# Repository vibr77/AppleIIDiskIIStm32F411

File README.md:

# SmartDisk II — Apple II Floppy Emulator

**The Apple II floppy emulator that even copy protection can't tell apart.**

Swap a shelf of aging 5.25″ disks for a single SD card — without giving up an ounce of authenticity. SmartDisk II reproduces the exact timing and behaviour of a real DISK II and UNIDISK 3.5 drive, so your games load and run exactly as they did back in the day — protection schemes and all.

<p align="center">
  <a href="https://www.ebay.fr/itm/306883712221"><b>🛒 Buy a prebuilt board</b></a> ·
  <a href="https://github.com/vibr77/AppleIIDiskIIStm32F411"><b>🔧 Build it yourself</b></a> ·
  <a href="https://discord.gg/ZnzDqC2k"><b>💬 Join the Discord</b></a> ·
  <a href="https://www.r3tr0.net/index.php/smartdisk-ii-documentation/"><b>📖 Documentation</b></a>
</p>

---

## What is it

SmartDisk II is an **open-source hardware floppy-disk emulator for the Apple II**. It plugs into your machine like a real drive, reads disk images straight from an SD card, and lets you browse and mount them from a built-in OLED menu — no PC, no cables, no fuss.

Under the hood it's built on the **STM32F411 ("BlackPill")** and emulates the disk hardware *at the bit level*. That's the difference between *reading a disk image* and *being a disk drive* — and it's why SmartDisk II runs the titles other emulators choke on.

## Why SmartDisk II

- **Bit-perfect accuracy.** Timing is reproduced down to the microsecond, so the Apple II can't tell it apart from a mechanical drive.
- **It beats copy protection.** Fake bits, weak bits, half-tracks, SpiraDisc and more — it passes every scheme tested so far.
- **Your whole collection on one card.** Thousands of disks on a single SD card, browsable on the on-board OLED.
- **Works across the Apple II line.** From the II+ to the IIGS, Disk II and SmartPort — one device covers your fleet.
- **Read *and* write.** Save your progress and modify disks, not just load them.
- **Open source, or ready to run.** Build it from the published files, or order a prebuilt, flashed board and plug in today.

## Browse and boot — right from the Apple II

With **SmartLoader**, you don't even need the SmartDisk II's own buttons for everyday loading. It puts a fast green-screen browser on the Apple II itself: SmartLoader reads the disk images on your SD card and lists them right on screen, so you can scroll through your whole collection and boot any title straight from the Apple II — highlight a disk, press **[B]** to boot, **[R]** to refresh the listing, or **[S]** for settings.

## Copy protection that actually works

Most emulators fall over the moment a disk uses copy protection. SmartDisk II doesn't. By reproducing the original drive's bit-level timing, it satisfies the protection checks that real software relied on — so your original protected images run untouched.

| Copy protection             | Status     |
|:----------------------------|:-----------|
| Fat Track                   | ✅ Passed |
| Weak Bit                    | ✅ Passed |
| Cross-track synchronisation | ✅ Passed |
| Half Track                  | ✅ Passed |
| Data Latch                  | ✅ Passed |
| Timing Bits                 | ✅ Passed |
| E7                          | ✅ Passed |
| Optimal Bit Timing (<4µs)   | ✅ Passed |
| Various Bit Counter         | ✅ Passed |
| SpiraDisc                   | ✅ Passed |

## Compatibility

| Apple II model | Emulation             |
|:---------------|:----------------------|
| II+            | Disk II               |
| II Europlus    | Disk II               |
| IIe            | Disk II               |
| IIc (ROM 4)    | Disk II + SmartPort   |
| IIGS           | Disk II + SmartPort   |

SmartPort emulation is also available on the IIc (ROM 4.x), IIGS, and on the II+/IIe with a Liron or SoftSP6 card.

## Supported disk formats

| Format  | Read | Write |
|:--------|:-----|:------|
| WOZ 2.0 | ✅   | ✅    |
| DSK     | ✅   | ✅    |
| PO      | ✅   | ✅    |
| 2MG     | ✅   | ✅    |
| WOZ 1.0 | ✅   | —     |
| NIC     | ✅   | —     |

## Features at a glance

- **Three drives in one** — DISK II 5.25″, SmartPort HD, and UNIDISK 3.5 emulation
- **On-board navigation** — browse, mount and unmount images from the 0.96″ OLED with four buttons
- **Big images, no sweat** — 32 MB images and full Total Replay collections run smoothly
- **Modern software too** — loads GS/OS on the IIGS; runs titles like Arkanoid from 2MG
- **SmartLoader** built in — browse and boot from the Apple II screen itself
- **Actively developed** — frequent firmware releases with the latest improvements

## See it in action

- ▶ [Total Replay & 32 MB images, running smoothly](https://www.youtube.com/watch?v=Sws6IjnWDGQ)
- ▶ [Arkanoid, loaded from a 2MG image](https://www.youtube.com/watch?v=U3N-gej0NLk)
- ▶ [Loading GS/OS on the IIGS](https://www.youtube.com/watch?v=gZH2njO4CEQ)

## Get your SmartDisk II

**Buy a prebuilt board.** Don't want to solder? Order a ready-to-use, fully flashed and tested SmartDisk II and plug in today → [Order on eBay](https://www.ebay.fr/itm/306883712221)

**Build it yourself.** Everything you need is open source — KiCad PCB, Gerber files, bill of materials, 3D-printable case, firmware releases and full source code. **Current production board: Revision 8**, recommended for self-builds.

**Get help & follow along.** Join the community on [Discord](https://discord.gg/6y2Zdazy), or read the full development story on [AppleFritter](https://www.applefritter.com/content/apple-ii-disk-emulator-using-stm32).

## Tech specs

- **MCU:** STM32F411 ("BlackPill") — chosen for CPU speed, >60 kB SRAM and 4-bit SDIO
- **Storage:** SD card, FAT32 (4-bit SDIO for speed) — a quality, known-brand card is recommended
- **Display:** 0.96″ OLED (SSD1306) with four-button navigation
- **Board:** Production Revision 8, fully tested
- **Licence:** open source for non-commercial use with attribution

---

# Build & developer guide

Everything below is for people building, flashing, or hacking on the SmartDisk II. The full end-user manual (wiring, SD-card prep, menu walkthrough) lives in the [online documentation](https://www.r3tr0.net/index.php/smartdisk-ii-documentation/).

## Firmware

The latest firmware (see the releases on the right-hand side of the GitHub page) requires **bootloader v0.14 or v0.16**. Version 0.15 is **not** compatible and causes issues with the IIGS SmartPort. It is recommended to update the bootloader to the latest version.

There are two release types:

- **BIN** — classic binary, uploaded via ST-Link, starting at `0x08000000`.
- **UF2** — first upload the custom bootloader via ST-Link, then connect USB and double-click the NRST button to drag-and-drop the UF2 release onto the STM32. **Warning:** with the bootloader, flash from `0x08000000` to `0x08100000` becomes read-only (use ST-Link tooling to change the STM32 register to reverse this).

## Project structure

| Directory            | Description                                          |
|:---------------------|:-----------------------------------------------------|
| `./hardware`         | KiCad project                                        |
| `./hardware/gerber`  | Gerber release to produce the PCB                    |
| `./hardware/bom`     | Bill of materials                                    |
| `./core`             | Firmware source code                                 |
| `./bootloader`       | Bootloader                                           |
| `./Middleware`       | Libraries used                                       |
| `./FATFS`            | FATFS wrapper                                         |
| `./doc`              | Documentation used as reference                      |
| `./3DPrintCase`      | 3D-print files & Fusion 360 source for the case      |

## SD card

The SD card must use a **FAT32 file system with 64 sectors of 512 bytes each per cluster (32 KB clusters)**.

To format the card under Linux:

```bash
mkfs.fat -F 32 -s 64 /dev/sdX
```

Windows 10/11 does **not** format the card the right way. A config-menu option is provided directly on the SmartDisk II to format the SD card correctly. Note that some SD cards have very poor read/write rates — use a known brand to avoid wasting your time.

## Important notes

- The ST-Link programmer should **never** be connected at the same time as either USB or the Apple II — its voltage regulator is fragile.
- The **J1 PWR** jumper (top-right of the PCB) enables +5 V from the Apple II to the STM32.
- OLED screen: be careful of the power-pin order; some versions have the pins inverted.
- R1, R2, R3 are not needed.
- Before hardware Rev 3, the board is not compatible with the IIGS & IIc — the trace between IDC pins 5 & 7 needs to be cut.
- Hardware design may evolve; new software releases might not work with older hardware revisions.

## Hardware design principles

The STM32F4x is preferred over the STM32F1 for CPU frequency, available SRAM (>60 kB), and (on the F411) SDIO. Timing is critical on this project, especially to pass copy protection.

A DISK II floppy track is about 50,000 bits, and shifting from one track to another must respect specific timing rules. After many design iterations, the chosen approach loads a **single track in memory** and uses the **4-bit SDIO port** for SD card read/write speed — avoiding adjacent-track management and complex buffer copies.

The Apple II expects data at a precise pace of **1 bit every 4 µs (32 × 125 ns)**. Three options were considered:

1. SDIO with DMA — frees the CPU, but SPI sends 8 bits at a time; WOZ tracks aren't 8-bit aligned, which introduces bit misalignment and corrupted data on protected images.
2. Assembly with CPU-cycle counting & GPIO bit-banging — poor reliability, discarded.
3. **Timer-interrupt-triggered GPIO bit-banging (chosen)** — frees CPU time for OLED updates and button handling, makes fake-bit/protection mechanisms easy to address, and allows fine timing control (e.g. 3.8 µs vs 4 µs that some games use).

The write process mirrors the read process with a dedicated timer overflowing every 4 µs; polarity inversion is handled in software with an XOR rather than external circuitry.

### STM32 pin mapping

**Head-positioning stepper (external interrupts):**
`PA0` STEP0 / ExtI0 · `PA1` STEP1 / ExtI1 · `PA2` STEP2 / ExtI2 · `PA3` STEP3 / ExtI3

**Other GPIO:**
`PB8` SELECT (ExtI8, HIGH on Disk II controller — A2 powered on) · `PB9` WR Request (ExtI9, active LOW when writing) · `PA4` Device Enable (ExtI4, active LOW) · `PB2` WR Protect · `PA7` WR Data · `PB0` RD Data · `PA11` _DISK3.5

**Buttons (ExtI 9-15, TIM4 debounce):**
`PC13` BTN_DOWN · `PC14` BTN_UP · `PC15` BTN_ENTR · `PB12` BTN_RET

**SD card (SDIO, clock ÷2):**
`PB4` D0 · `PA8` D1 · `PA9` D2 · `PB5` D3 · `PA6` CMD · `PB15` CK

**OLED SSD1306 (I²C):** `PB6` SCL · `PB7` SDA

**UART:** `PA15` TX · `PB3` RX

**Timers:**
- **TIM2** — manages WR_DATA; ETR1 slave-reset mode resyncs with the Apple II write pulse (3.958 µs instead of 4 µs) on every rising edge.
- **TIM3** — manages RD_DATA.
- **TIM4** — internal (no PWM), debouncer for the control buttons.

## Software design principles

Built on:

- STM32 HAL drivers from STMicro
- FATFS 0.15 (note: STM32CubeMX overrides to 0.11)
- cJSON for the configuration file (tweaked to work with FATFS)
- SSD1306 library with DMA

Maximum track size is `13 × 512 × 8 = 53,248` bits (6,656 bytes), held in `DMA_BIT_TX_BUFFER[6656]`. `weakBitTank` (uint8 array) and `fakeBitTank` (char array) manage copy-protection mechanisms.

**Key functions:**

- `TIM3_IRQHandler` — bit-bangs the GPIO to send track data every 4 µs (or less, per WOZ config) to the Apple II.
- `TIM2_IRQHandler` — handles data sent from the Apple II for writing; uses a software XOR to detect polarity inversion and writes 1/0 to `DMA_BIT_RX_BUFFER`.
- `irqReadTrack` / `irqWriteTrack` — configure read/write interrupts.
- `getDataBlocksBareMetal(...)` / `setDataBlocksBareMetal(...)` — direct SDIO access to the SD card, faster than FATFS `f_open`. (FATFS is still required to build the file allocation table with correct block addresses.)
- `processDeviceEnableInterrupt` — activates/deactivates the Disk II drive on the DEVICE_ENABLE pin (active LOW).
- `processBtnInterrupt` — handles the four buttons.
- `processDiskHeadMoveInterrupt(...)` — handles the four stepper-motor GPIOs.
- `main()` — orchestrates program execution.

A **ST-Link** programmer is required to upload firmware to the STM32F411.

## Bill of materials

Interactive BOM: [SmartDisk II Bill of Material](https://vibr77.github.io/AppleIIDiskIIStm32F411/hardware/bom/ibom.html)

## Recommended reading

WOZ 2.1 & 1.0 image file references · Tome of Copy Protection · Beneath Apple DOS · Assembly Lines · Understanding the Apple II · PoC‖GTFO issues 10 & 11 · IIGS Firmware Reference · IIc Programmer's Guide to the 3.5 ROM (part 2)

## Licence

This project may be distributed, remixed, adapted and built upon, in any medium or format, **for non-commercial purposes only**, and only with attribution to the creator. Commercial rights are reserved to the author.

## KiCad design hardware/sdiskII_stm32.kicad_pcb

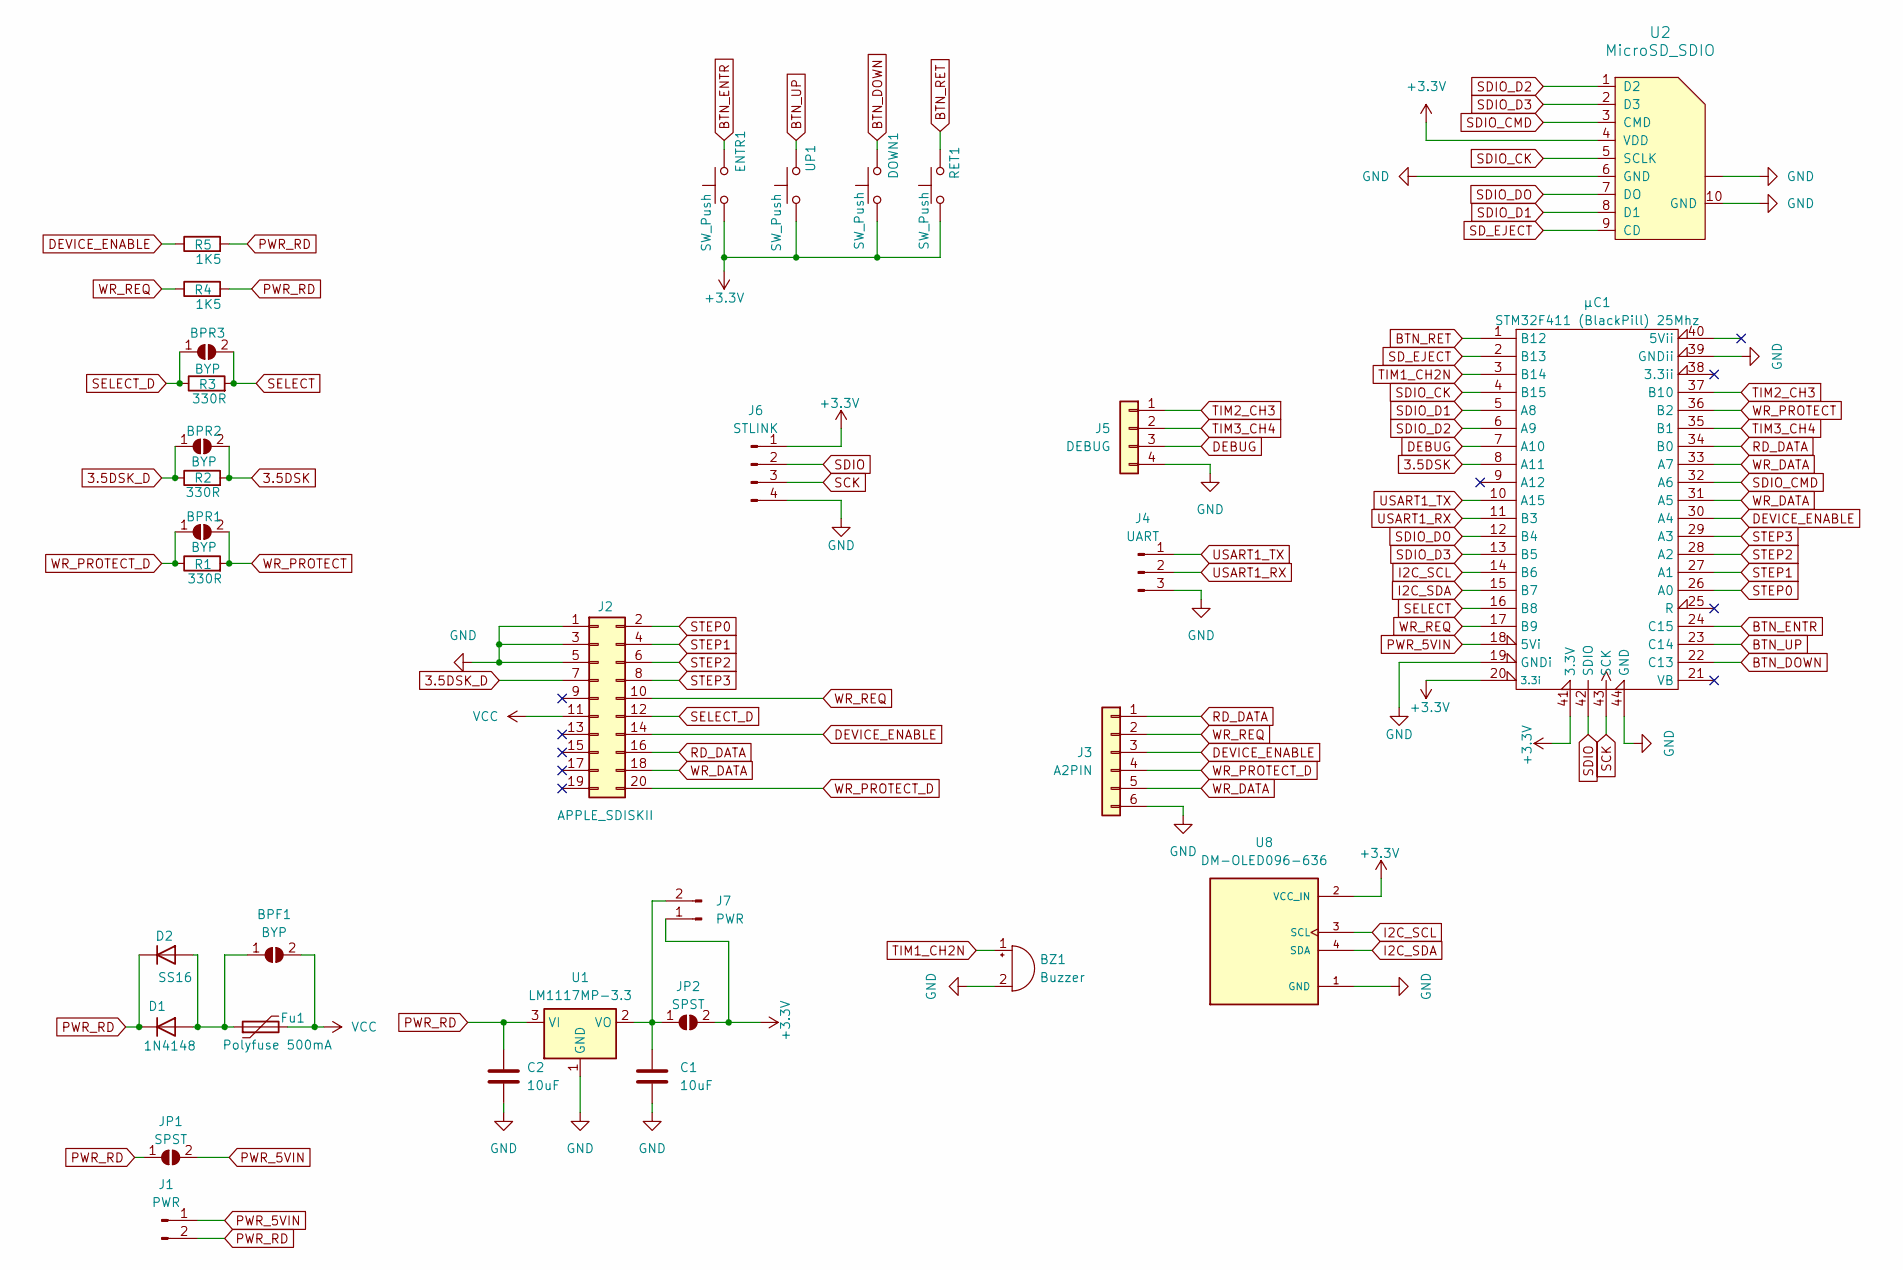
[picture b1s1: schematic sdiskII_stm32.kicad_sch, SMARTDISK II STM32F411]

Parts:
BPF1: BYP; SolderJumper-2_P1.3mm_Open_RoundedPad1.0x1.5mm
BPR1, BPR2, BPR3: BYP; SolderJumper-2_P1.3mm_Open_RoundedPad1.0x1.5mm
BZ1: Buzzer; AS-1201B-LF
C1, C2: 10uF; C_0805_2012Metric_Pad1.18x1.45mm_HandSolder
D1: 1N4148; D_DO-35_SOD27_P7.62mm_Horizontal
D2: SS16; D_SMA_Handsoldering
DOWN1: SW_Push; SW_PUSH_6mm
ENTR1: SW_Push; SW_PUSH_6mm
Fu1: Polyfuse 500mA; Fuse_0805_2012Metric_Pad1.15x1.40mm_HandSolder
J1, J7: PWR; PinHeader_1x02_P2.54mm_Vertical
J2: APPLE_SDISKII; IDC-Header_2x10_P2.54mm_Vertical
J3: A2PIN; PinHeader_1x06_P2.54mm_Vertical
J4: UART; PinHeader_1x03_P2.54mm_Vertical
J5: DEBUG; PinHeader_1x04_P2.54mm_Vertical
J6: STLINK; PinHeader_1x04_P2.54mm_Vertical
JP1, JP2: SPST; SolderJumper-2_P1.3mm_Open_RoundedPad1.0x1.5mm
R1, R2, R3: 330R; R_0805_2012Metric_Pad1.20x1.40mm_HandSolder
R4, R5: 1K5; R_0805_2012Metric_Pad1.20x1.40mm_HandSolder
RET1: SW_Push; SW_PUSH_6mm
U1: LM1117MP-3.3; SOT-223-3_TabPin2
U2: MicroSD_SDIO; GCT-MEM2055-00-190-01-A_VIB
U8: DM-OLED096-636; MODULE_DM-OLED096-636; PARTREV 2018-09-10
UP1: SW_Push; SW_PUSH_6mm
μC1: STM32F411 (BlackPill) 25Mhz; Mini_F4X1_STM32_VIB

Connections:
3.5DSK: BPR2.2 (B), R2.2, μC1.8 (A11)
3.5DSK_D: BPR2.1 (A), J2.7, R2.1
+3.3V: DOWN1.1, ENTR1.1, J6.1, J7.1, JP2.2 (B), RET1.1, U2.4 (VDD), U8.2 (VCC_IN), UP1.1, μC1.20 (3.3i), μC1.41 (3.3V)
BTN_DOWN: DOWN1.2, μC1.22 (C13)
BTN_ENTR: ENTR1.2, μC1.24 (C15)
BTN_RET: RET1.2, μC1.1 (B12)
BTN_UP: UP1.2, μC1.23 (C14)
DEBUG: J5.3, μC1.7 (A10)
DEVICE_ENABLE: J2.14, J3.3, R5.1, μC1.30 (A4)
GND: BZ1.2 (-), C1.2, C2.2, J2.1, J2.3, J2.5, J3.6, J4.3, J5.4, J6.4, U1.1 (GND), U2.6 (GND), U2.10 (GND), U2.~, U8.1 (GND), μC1.19 (GNDi), μC1.39 (GNDii), μC1.44 (GND)
I2C_SCL: U8.3 (SCL), μC1.14 (B6)
I2C_SDA: U8.4 (SDA), μC1.15 (B7)
unnamed: BPF1.1 (A), D1.2 (A), D2.2 (A), Fu1.1
unnamed: C1.1, J7.2, JP2.1 (A), U1.2 (VO)
PWR_5VIN: J1.1, JP1.2 (B), μC1.18 (5Vi)
PWR_RD: C2.1, D1.1 (K), D2.1 (K), J1.2, JP1.1 (A), R4.2, R5.2, U1.3 (VI)
RD_DATA: J2.16, J3.1, μC1.34 (B0)
SCK: J6.3, μC1.43 (SCK)
SDIO: J6.2, μC1.42 (SDIO)
SDIO_CK: U2.5 (SCLK), μC1.4 (B15)
SDIO_CMD: U2.3 (CMD), μC1.32 (A6)
SDIO_D1: U2.8 (D1), μC1.5 (A8)
SDIO_D2: U2.1 (D2), μC1.6 (A9)
SDIO_D3: U2.2 (D3), μC1.13 (B5)
SDIO_DO: U2.7 (DO), μC1.12 (B4)
SD_EJECT: U2.9 (CD), μC1.2 (B13)
SELECT: BPR3.2 (B), R3.2, μC1.16 (B8)
SELECT_D: BPR3.1 (A), J2.12, R3.1
STEP0: J2.2, μC1.26 (A0)
STEP1: J2.4, μC1.27 (A1)
STEP2: J2.6, μC1.28 (A2)
STEP3: J2.8, μC1.29 (A3)
TIM1_CH2N: BZ1.1 (+), μC1.3 (B14)
TIM2_CH3: J5.1, μC1.37 (B10)
TIM3_CH4: J5.2, μC1.35 (B1)
USART1_RX: J4.2, μC1.11 (B3)
USART1_TX: J4.1, μC1.10 (A15)
VCC: BPF1.2 (B), Fu1.2, J2.11
WR_DATA: J2.18, J3.5, μC1.31 (A5), μC1.33 (A7)
WR_PROTECT: BPR1.2 (B), R1.2, μC1.36 (B2)
WR_PROTECT_D: BPR1.1 (A), J2.20, J3.4, R1.1
WR_REQ: J2.10, J3.2, R4.1, μC1.17 (B9)

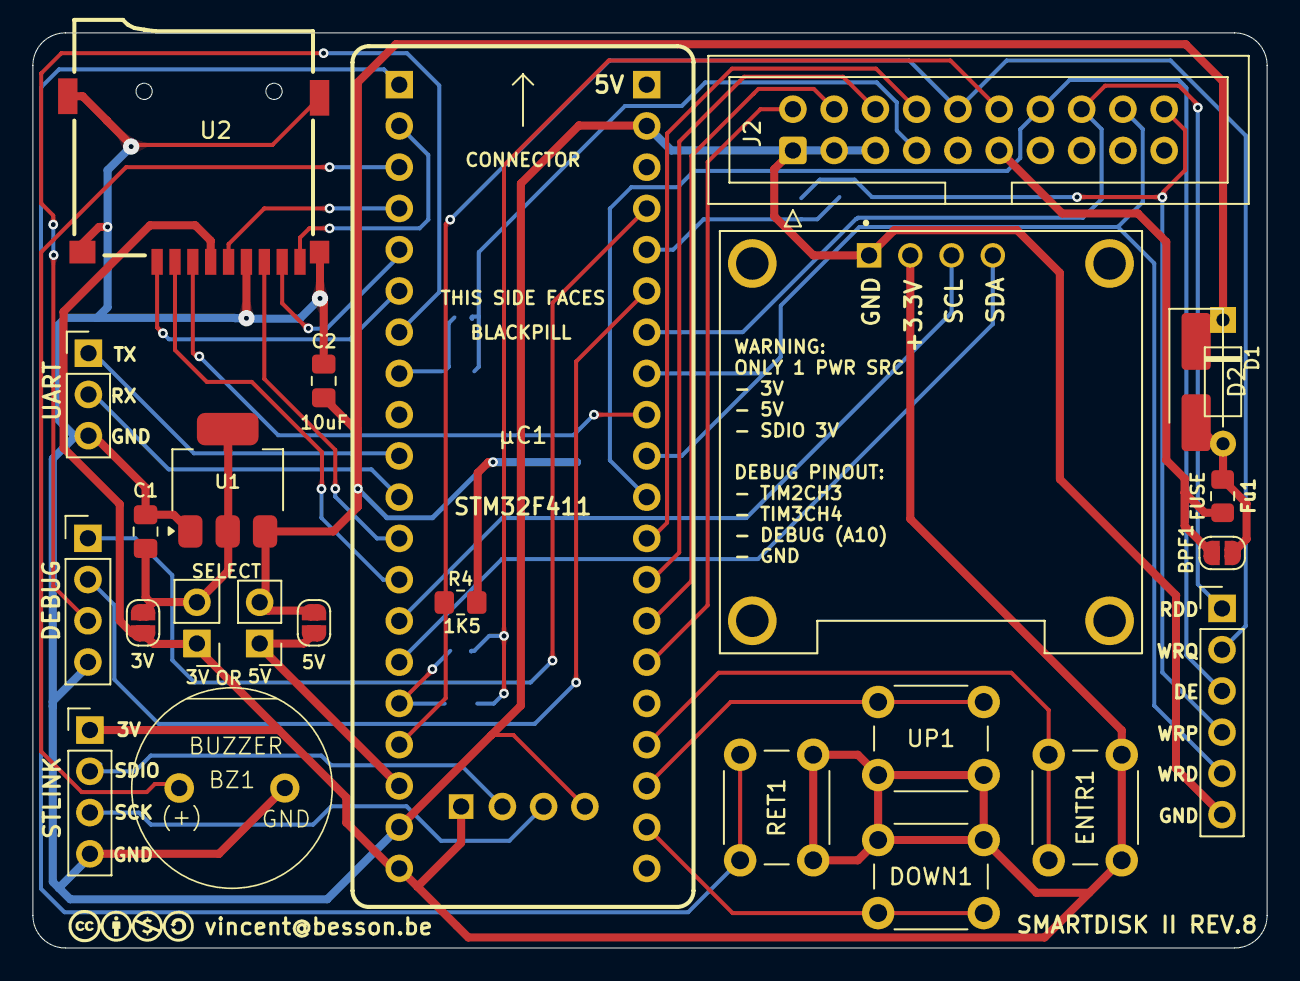
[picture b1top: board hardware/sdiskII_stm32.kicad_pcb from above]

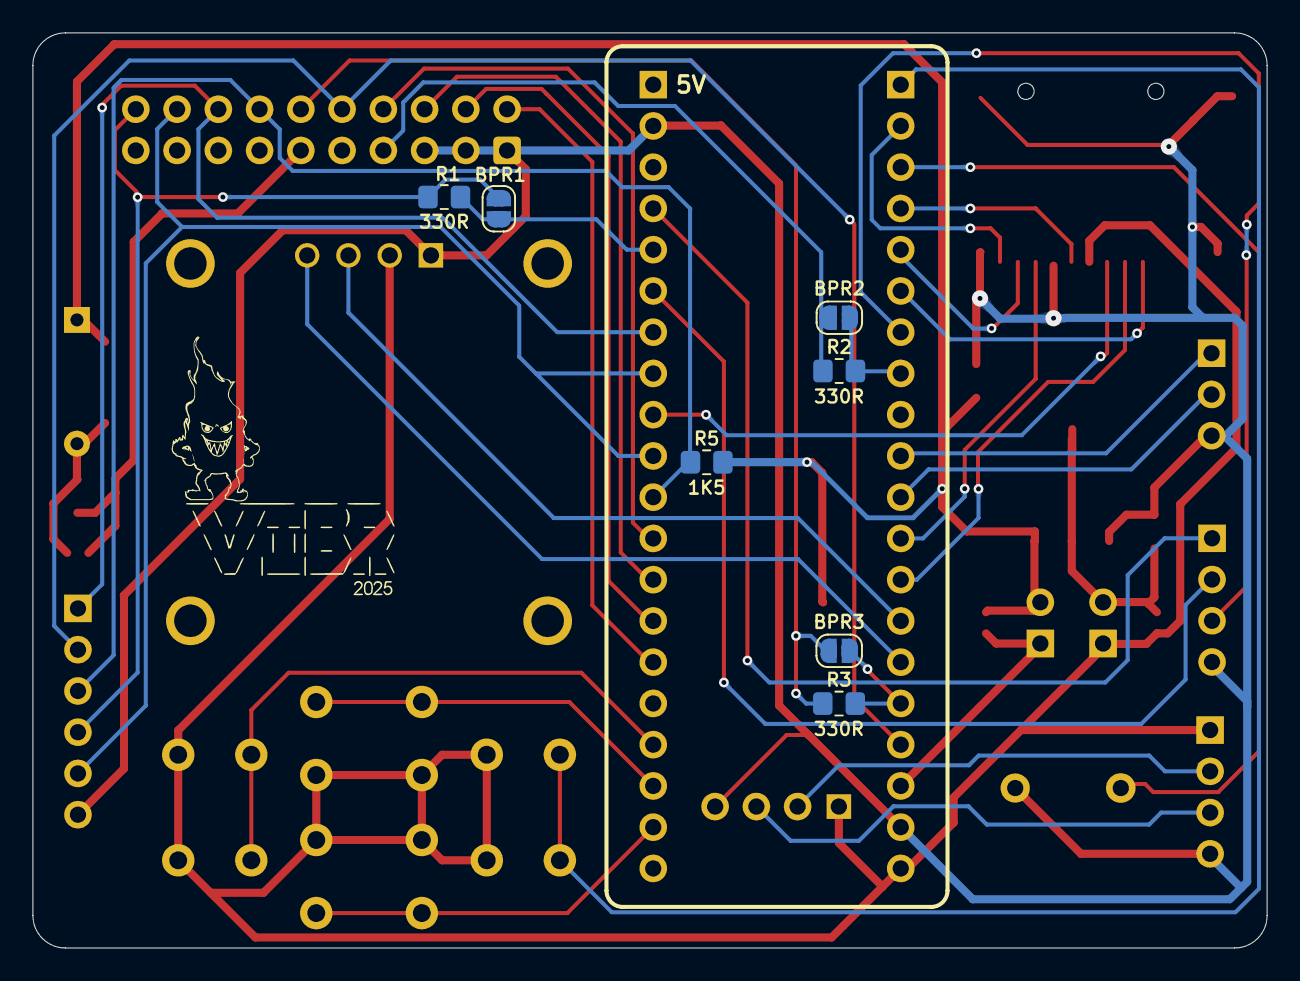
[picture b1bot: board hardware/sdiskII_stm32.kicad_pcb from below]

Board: 2 copper layers, 76.0 x 56.3 mm, 33 parts (7 on the bottom side), 42 nets.

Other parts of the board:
 : LOGO

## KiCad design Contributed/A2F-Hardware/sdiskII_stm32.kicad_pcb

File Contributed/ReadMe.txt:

### VIBR SmartDisk II - Apple II forever modification ###

https://youtube.com/shorts/TgZ5UqMbQsM

https://github.com/joergschne/AppleIIDiskIIStm32F411

https://developer.arm.com/downloads/-/arm-gnu-toolchain-downloads

export PATH="/Applications/ArmGNUToolchain/13.3.rel1/arm-none-eabi/bin:$PATH"

Download mandatory STM32F4xx driver at: https://www.st.com/en/development-tools/stm32cubemx.html

# Driver/BSP
# Driver/CMSIS
# Driver/STM32F4xx_HAL_Driver

Build with Apple II forever mode: make -f Makefile USE_BOOTLOADER=1 A2F_MODE=1 

# python uf2conv/uf2conv.py -b 0x08010000 -f STM32F4 -o build/AppleIISDiskII_stm32f411_sdio.uf2 build/AppleIISDiskII_stm32f411_sdio.bin

BOM:
https://shop.lcd-module.de/128x64-OLED-YELLOW/OLEDM128-6LGA
or
https://shop.lcd-module.de/OLED128x64green-COG/W128064-XALE

1	311-1344-1-ND			CC0603KRX7R9BB104	CAP CER 0.1UF 50V X7R 0603		1
2	478-1655-1-ND			TAJA106K016RNJ		CAP TANT 10UF 10% 16V 1206		3
3	732-2096-ND			61202021621		CONN HEADER VERT 20POS 2.54MM		2
4	296-SN74LS257BDRCT-ND		SN74LS257BDR		IC MULTIPLEXER 4 X 2:1 16SOIC		1
5	4809-RKJXT1F42001-ND		RKJXT1F42001		SWITCH JOYSTICK ANALOG 10MA 5V		1
6	664-GMC020080HRCT-ND		GMC020080HR		CONN SD/MMC/MS CARD R/A SMD		1
7	102-1266-1-ND	CT-1205H-SMT-TR	BUZZER MAGNETIC 5V 12.8X12.8 SMD				1
8	311-10KLGCT-ND	AC0805FR-0710KL	RES SMD 10K OHM 1% 1/8W 0805					12
9	13-AC0805FR-07910KLCT-ND	AC0805FR-07910KL	RES SMD 910K OHM 1% 1/8W 0805		1
10	P12937SCT-ND			EVQ-Q2F03W		SWITCH TACTILE SPST-NO 0.02A 15V	4
11	MICRO SD-CARD SMD		GCT-MEM2055-00-190-01-A_VIB					1
12	LED 5 mm
13	Buchsenleisten 2,54 mm
14	Flachbandkabel und 20P Pfosten-Steckverbinder
15	STM32F411 (Black Pill) Board

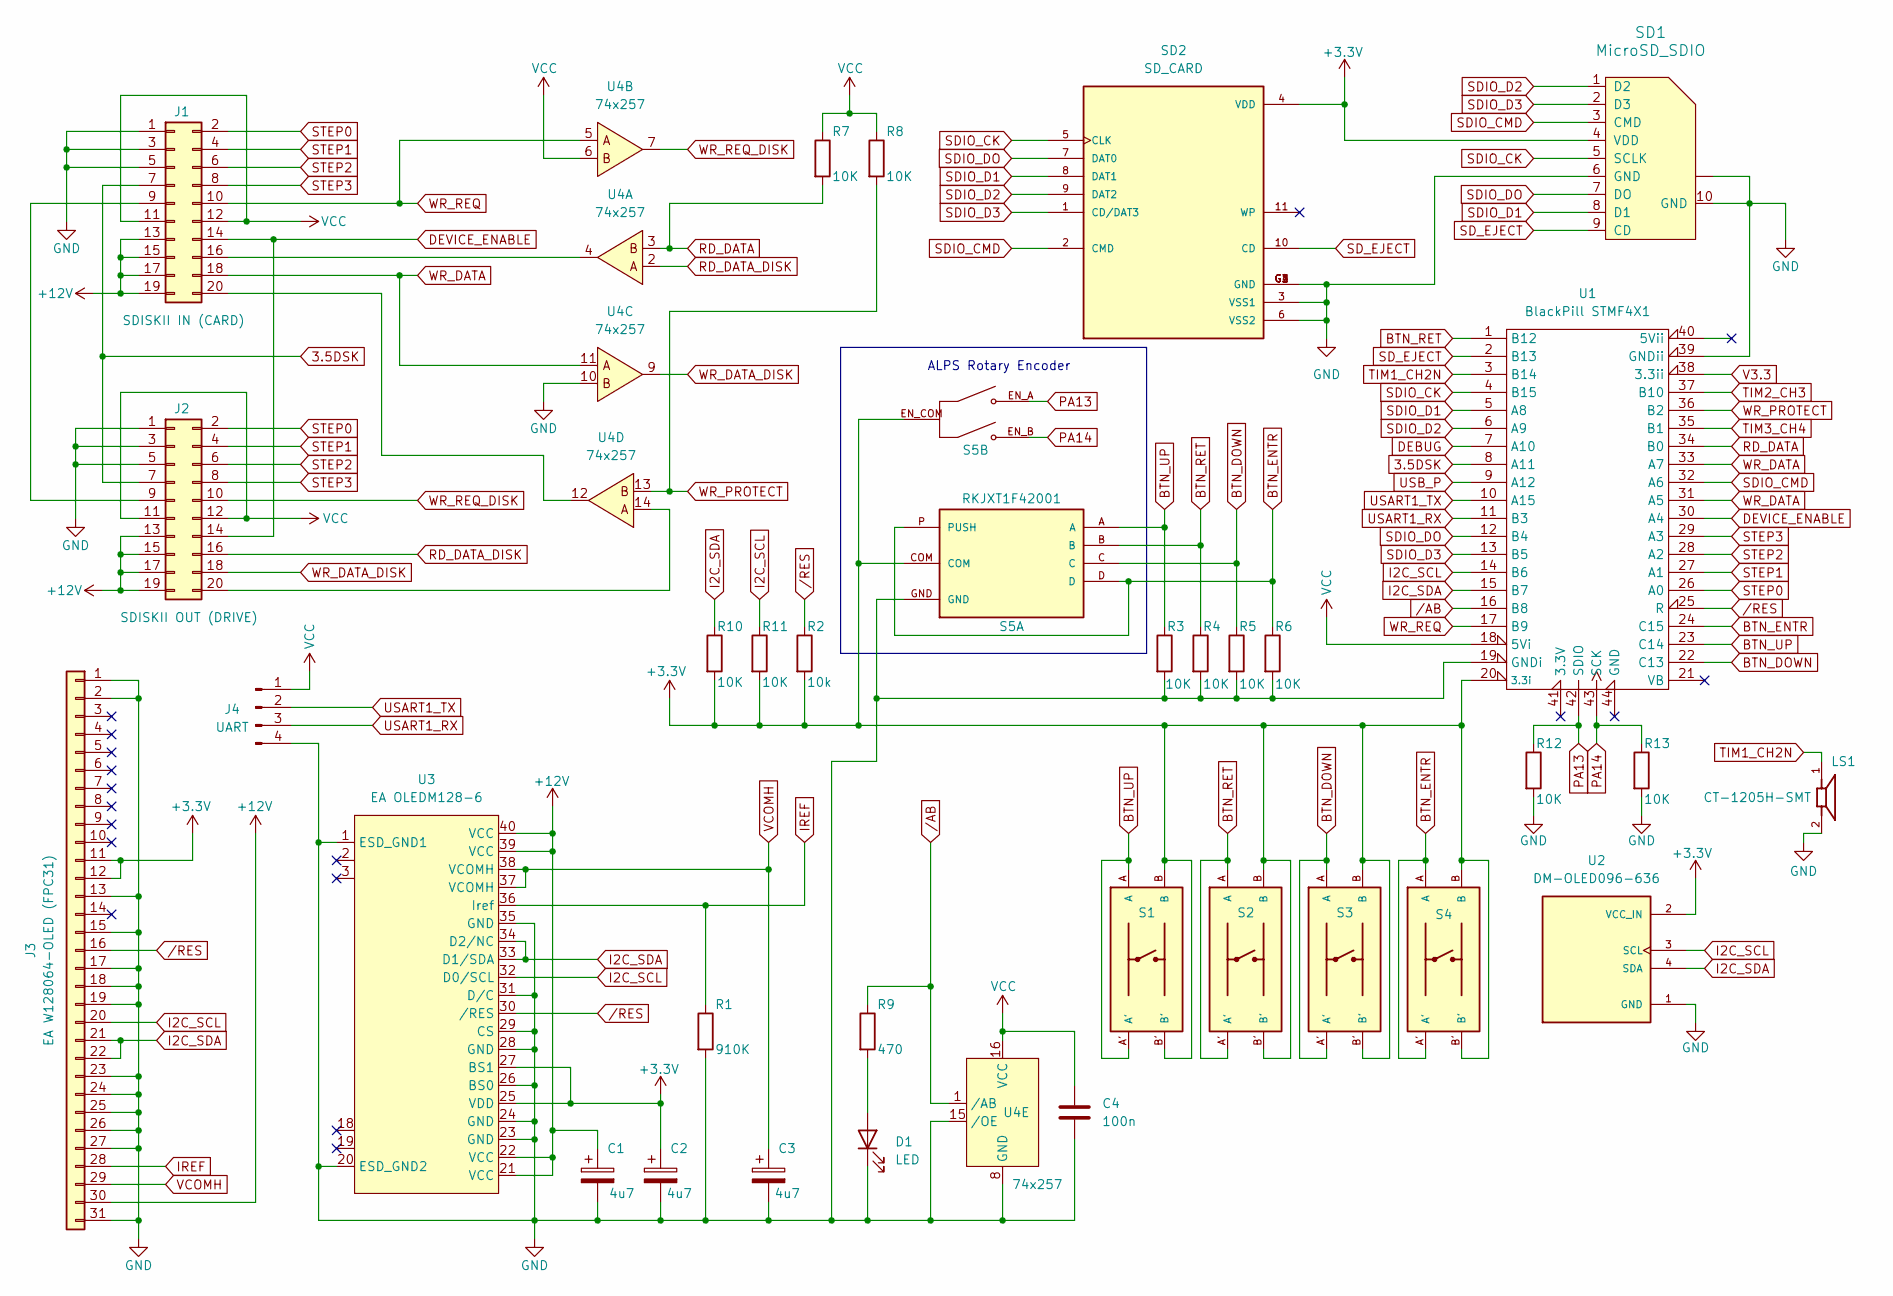
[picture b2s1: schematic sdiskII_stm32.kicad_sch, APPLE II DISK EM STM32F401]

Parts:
C1, C2, C3: 4u7; CP_EIA-3216-18_Kemet-A_Pad1.58x1.35mm_HandSolder
C4: 100n; C_0805_2012Metric_Pad1.18x1.45mm_HandSolder
D1: LED; LED_D3.0mm
J1: SDISKII IN (CARD); IDC-Header_2x10_P2.54mm_Vertical
J2: SDISKII OUT (DRIVE); IDC-Header_2x10_P2.54mm_Vertical
J3: EA W128064-OLED (FPC31); AMPHENOL_F32R-1A7H1-11031
J4: UART; PinHeader_1x04_P2.54mm_Vertical
LS1: CT-1205H-SMT; BUZZER CUI_CT-1205H-SMT; PART_REV 1.02
R1: 910K; R_0805_2012Metric_Pad1.20x1.40mm_HandSolder
R2: 10k; R_0805_2012Metric_Pad1.20x1.40mm_HandSolder
R3, R4, R5, R6, R7, R8, R10, R11, R12, R13: 10K; R_0805_2012Metric_Pad1.20x1.40mm_HandSolder
R9: 470; R_0805_2012Metric_Pad1.20x1.40mm_HandSolder
S1, S2, S3, S4: EVQ-Q2B02W; SW_EVQ-Q2B02W
S5: RKJXT1F42001; ALPS XDCR_RKJXT1F42001
SD1: MicroSD_SDIO; GCT-MEM2055-00-190-01-A_VIB
SD2: SD_CARD; SD_CARD_AMPHENOL_GMC020080HR; PARTREV AX6
U1: BlackPill STMF4X1; Mini_F4X1_STM32_VIB
U2: DM-OLED096-636; MODULE_DM-OLED096-636-SMAL; PARTREV 2018-09-10
U3: EA OLEDM128-6
U4: 74x257; SOIC-16_3.9x9.9mm_P1.27mm

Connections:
3.5DSK: J1.7, J2.7, U1.8 (A11)
+3.3V: C2.1, J3.11, J3.12, R2.2, R10.2, R11.2, S1.B, S1.B', S2.B, S2.B', S3.B, S3.B', S4.B, S4.B', S5.COM, S5.EN_COM, SD1.4 (VDD), SD2.4 (VDD), U1.20 (3.3i), U2.2 (VCC_IN), U3.25 (VDD), U3.27 (BS1)
+12V: C1.1, J1.13, J1.15, J1.17, J1.19, J2.13, J2.15, J2.17, J2.19, J3.30, U3.21 (VCC), U3.22 (VCC), U3.39 (VCC), U3.40 (VCC)
BTN_DOWN: R5.1, S3.A, S3.A', S5.C, U1.22 (C13)
BTN_ENTR: R6.1, S4.A, S4.A', S5.D, S5.P (PUSH), U1.24 (C15)
BTN_RET: R4.1, S2.A, S2.A', S5.B, U1.1 (B12)
BTN_UP: R3.1, S1.A, S1.A', S5.A, U1.23 (C14)
DEBUG: U1.7 (A10)
DEVICE_ENABLE: J1.14, J2.14, U1.30 (A4)
GND: C1.2, C2.2, C3.2, C4.2, D1.1 (K), J1.1, J1.3, J1.5, J2.1, J2.3, J2.5, J3.1, J3.2, J3.13, J3.15, J3.17, J3.18, J3.19, J3.23, J3.24, J3.25, J3.26, J3.27, J3.31, J4.4, LS1.2, R1.2, R3.2, R4.2, R5.2, R6.2, R12.2, R13.2, S5.GND, SD1.6 (GND), SD1.10 (GND), SD1.~, SD2.3 (VSS1), SD2.6 (VSS2), SD2.G1 (GND), SD2.G2 (GND), SD2.G3 (GND), SD2.G4 (GND), U1.19 (GNDi), U1.39 (GNDii), U2.1 (GND), U3.1 (ESD_GND1), U3.20 (ESD_GND2), U3.23 (GND), U3.24 (GND), U3.26 (BS0), U3.28 (GND), U3.29 (CS), U3.31 (D/C), U3.35 (GND), U4.8 (GND), U4.10, U4.15 (/OE)
I2C_SCL: J3.20, R11.1, U1.14 (B6), U2.3 (SCL), U3.32 (D0/SCL)
I2C_SDA: J3.21, J3.22, R10.1, U1.15 (B7), U2.4 (SDA), U3.33 (D1/SDA), U3.34 (D2/NC)
IREF: J3.28, R1.1, U3.36 (Iref)
unnamed: D1.2 (A), R9.2
unnamed: J1.9, J2.9
unnamed: J1.16, U4.4
unnamed: J1.20, U4.12
unnamed: J2.20, U4.14
PA13: R12.1, S5.EN_A, U1.42 (SDIO)
PA14: R13.1, S5.EN_B, U1.43 (SCK)
RD_DATA: R7.2, U1.34 (B0), U4.3
RD_DATA_DISK: J2.16, U4.2
SDIO_CK: SD1.5 (SCLK), SD2.5 (CLK), U1.4 (B15)
SDIO_CMD: SD1.3 (CMD), SD2.2 (CMD), U1.32 (A6)
SDIO_D1: SD1.8 (D1), SD2.8 (DAT1), U1.5 (A8)
SDIO_D2: SD1.1 (D2), SD2.9 (DAT2), U1.6 (A9)
SDIO_D3: SD1.2 (D3), SD2.1 (CD/DAT3), U1.13 (B5)
SDIO_DO: SD1.7 (DO), SD2.7 (DAT0), U1.12 (B4)
SD_EJECT: SD1.9 (CD), SD2.10 (CD), U1.2 (B13)
STEP0: J1.2, J2.2, U1.26 (A0)
STEP1: J1.4, J2.4, U1.27 (A1)
STEP2: J1.6, J2.6, U1.28 (A2)
STEP3: J1.8, J2.8, U1.29 (A3)
TIM1_CH2N: LS1.1, U1.3 (B14)
TIM2_CH3: U1.37 (B10)
TIM3_CH4: U1.35 (B1)
USART1_RX: J4.3, U1.11 (B3)
USART1_TX: J4.2, U1.10 (A15)
USB_P: U1.9 (A12)
V3.3: U1.38 (3.3ii)
VCC: C4.1, J1.11, J1.12, J2.11, J2.12, J4.1, R7.1, R8.1, U1.18 (5Vi), U4.6, U4.16 (VCC)
VCOMH: C3.1, J3.29, U3.37 (VCOMH), U3.38 (VCOMH)
WR_DATA: J1.18, U1.31 (A5), U1.33 (A7), U4.11
WR_DATA_DISK: J2.18, U4.9
WR_PROTECT: R8.2, U1.36 (B2), U4.13
WR_REQ: J1.10, U1.17 (B9), U4.5
WR_REQ_DISK: J2.10, U4.7
/AB: R9.1, U1.16 (B8), U4.1 (/AB)
/RES: J3.16, R2.1, U1.25 (R), U3.30 (/RES)

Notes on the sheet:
ALPS Rotary Encoder

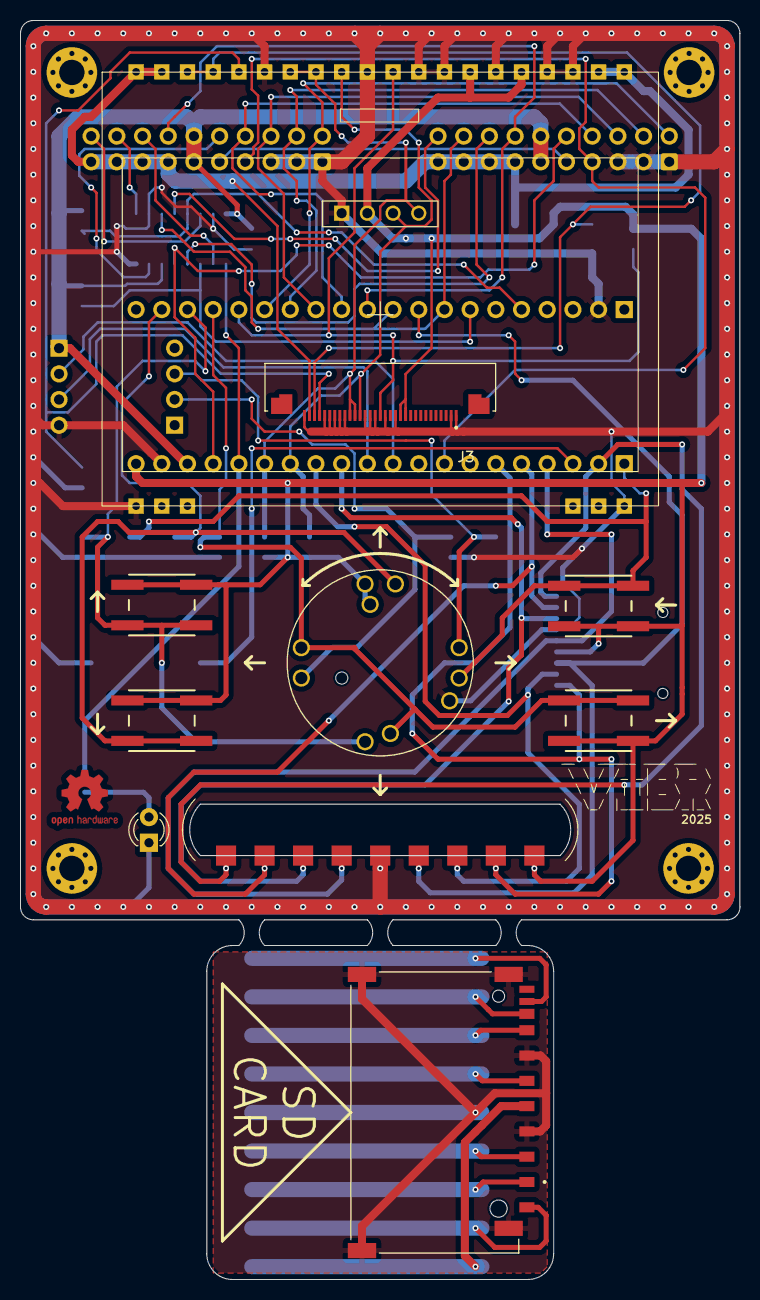
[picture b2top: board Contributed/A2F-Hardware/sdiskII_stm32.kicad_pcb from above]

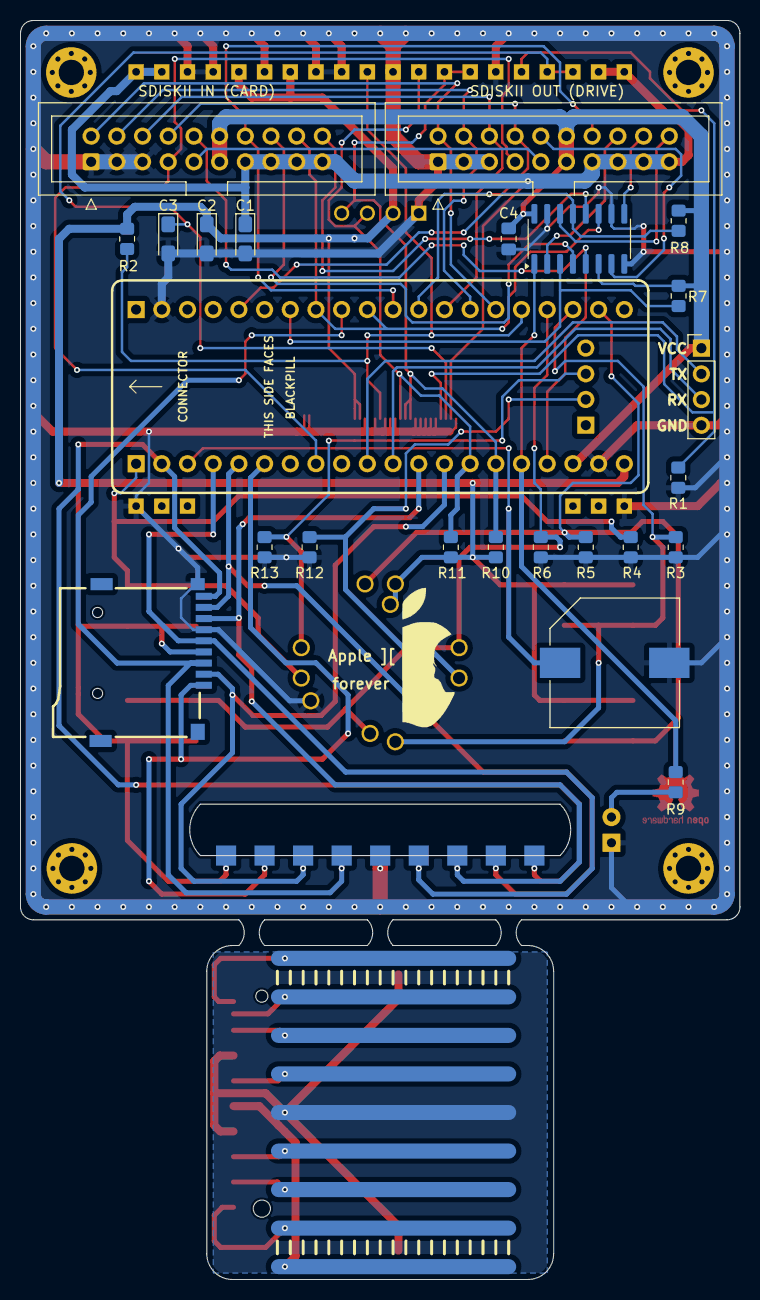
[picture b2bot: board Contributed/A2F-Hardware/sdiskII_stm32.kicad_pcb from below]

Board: 2 copper layers, 71.1 x 124.5 mm, 39 parts (24 on the bottom side), 44 nets.

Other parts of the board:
H1, H2, H3, H4: MountingHole_2.5mm_Pad_Via
VIBR: LOGO

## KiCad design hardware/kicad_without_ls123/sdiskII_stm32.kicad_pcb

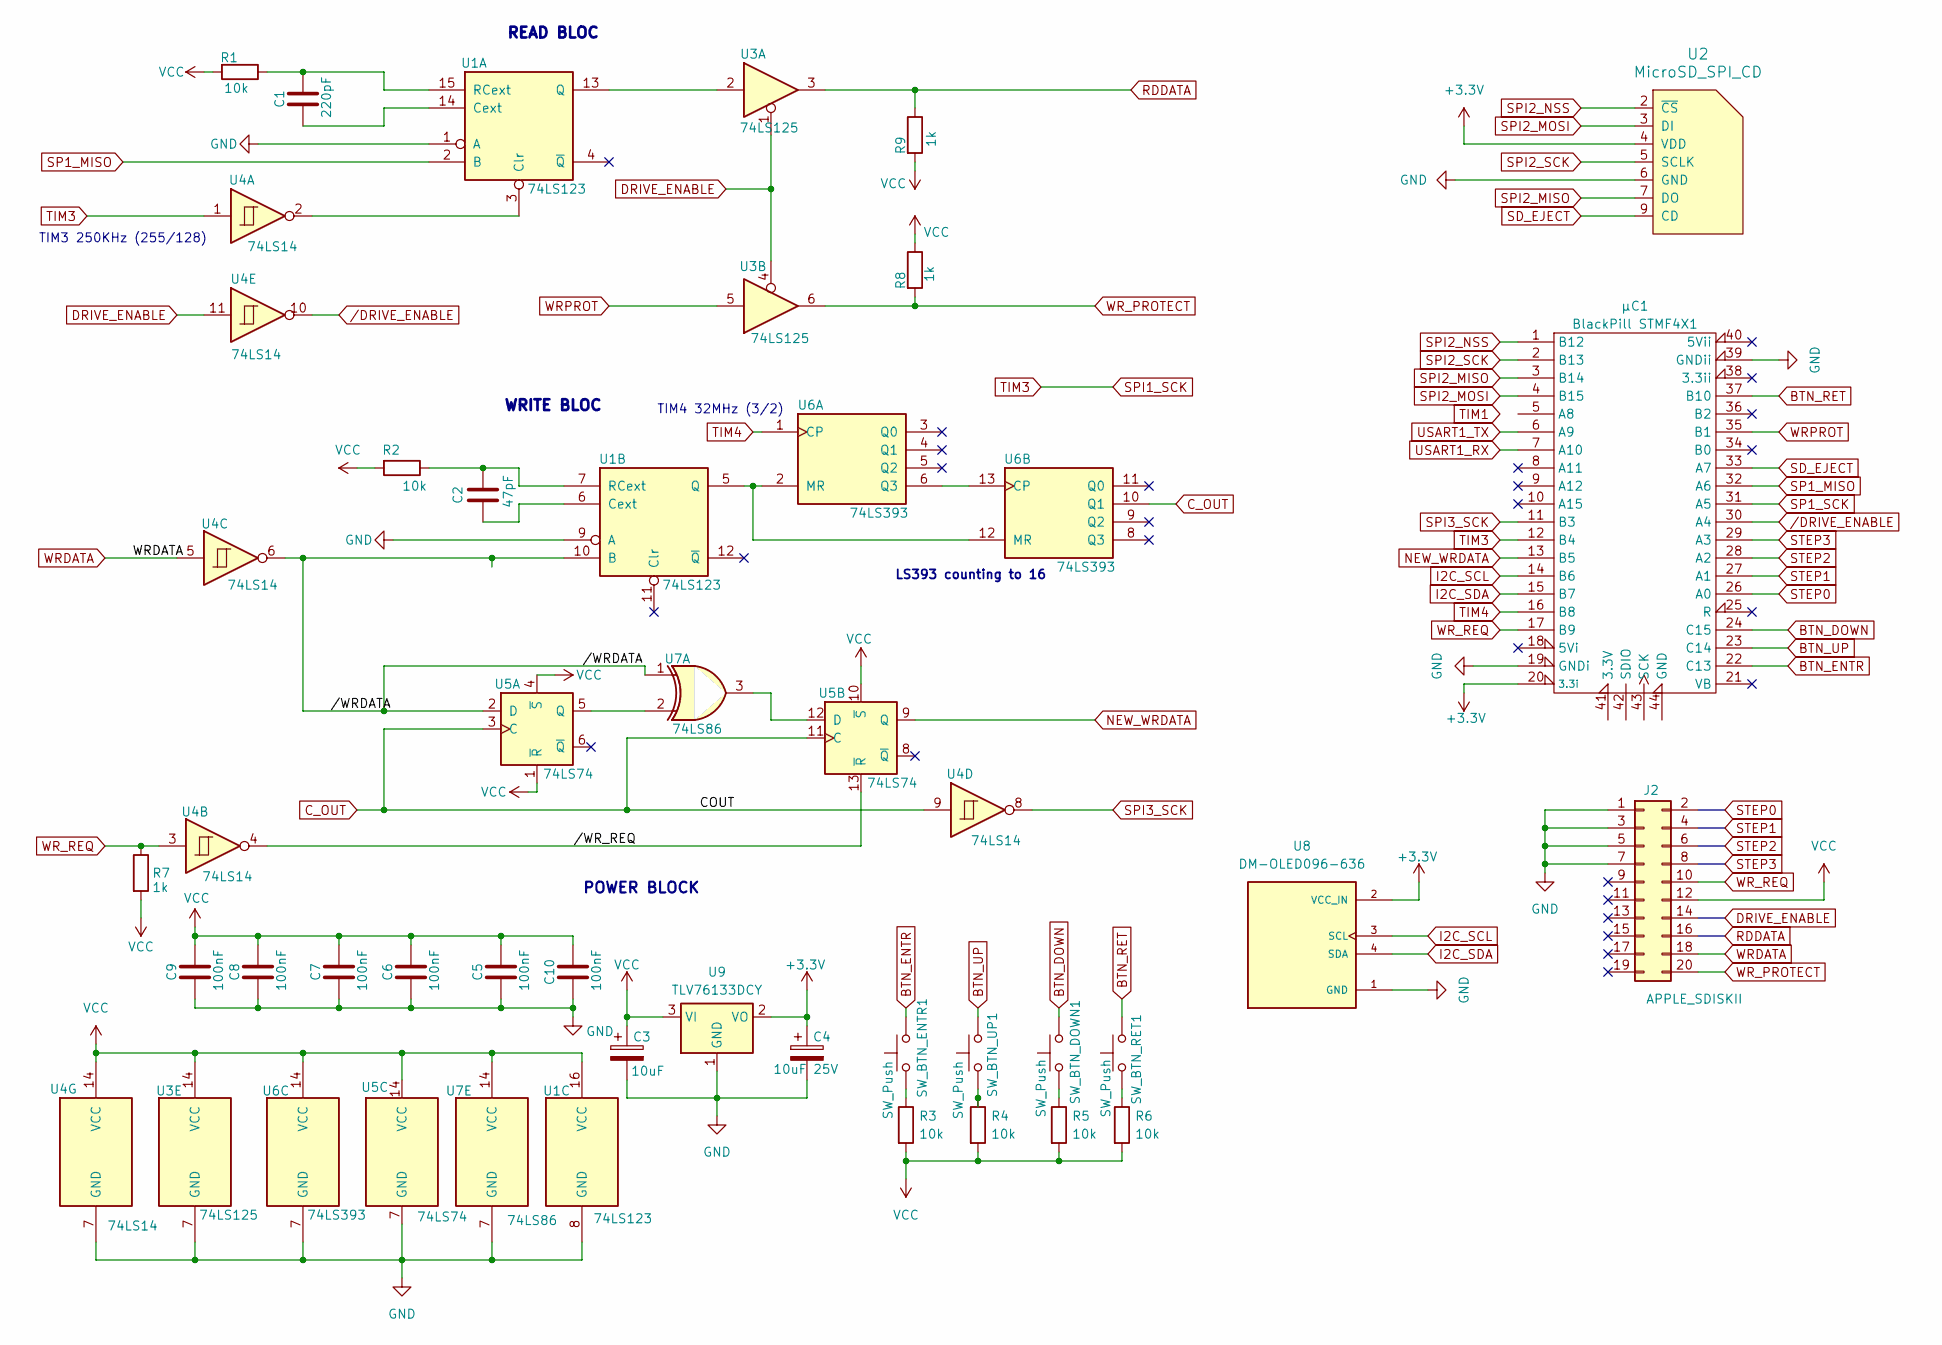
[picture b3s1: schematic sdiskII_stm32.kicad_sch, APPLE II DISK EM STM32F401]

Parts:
C1: 220pF; C_Disc_D5.0mm_W2.5mm_P5.00mm
C2: 47pF; C_Disc_D5.0mm_W2.5mm_P5.00mm
C3: 10uF; CP_Radial_D5.0mm_P2.50mm
C4: 10uF 25V; CP_Radial_D5.0mm_P2.50mm
C5, C6, C7, C8, C9, C10: 100nF; C_Disc_D5.0mm_W2.5mm_P5.00mm
J2: APPLE_SDISKII; IDC-Header_2x10_P2.54mm_Vertical
R1, R2, R3, R4, R5, R6: 10k; R_Axial_DIN0207_L6.3mm_D2.5mm_P7.62mm_Horizontal
R7, R8, R9: 1k; R_Axial_DIN0207_L6.3mm_D2.5mm_P7.62mm_Horizontal
SW_BTN_DOWN1: SW_Push; SW_PUSH_6mm
SW_BTN_ENTR1: SW_Push; SW_PUSH_6mm
SW_BTN_RET1: SW_Push; SW_PUSH_6mm
SW_BTN_UP1: SW_Push; SW_PUSH_6mm
U1: 74LS123; DIP-16_W7.62mm
U2: MicroSD_SPI_CD; GCT-MEM2055-00-190-01-A
U3: 74LS125; DIP-14_W7.62mm
U4: 74LS14; DIP-14_W7.62mm
U5: 74LS74; DIP-14_W7.62mm
U6: 74LS393; DIP-14_W7.62mm
U7: 74LS86; DIP-14_W7.62mm
U8: DM-OLED096-636; MODULE_DM-OLED096-636; PARTREV 2018-09-10
U9: TLV76133DCY; SOT-223-3_TabPin2
μC1: BlackPill STMF4X1; Mini_F4X1_STM32

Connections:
+3.3V: C4.1, U2.4 (VDD), U8.2 (VCC_IN), U9.2 (VO), μC1.20 (3.3i)
//WRDATA: U1.10 (B), U4.6, U5.2 (D), U7.1
//WR_REQ: U4.4, U5.13 (~R)
BTN_DOWN: SW_BTN_DOWN1.2, μC1.24 (C15)
BTN_ENTR: SW_BTN_ENTR1.2, μC1.22 (C13)
BTN_RET: SW_BTN_RET1.2, μC1.37 (B10)
BTN_UP: SW_BTN_UP1.2, μC1.23 (C14)
C_OUT: U4.9, U5.3 (C), U5.11 (C), U6.10 (Q1)
DRIVE_ENABLE: J2.14, U3.1, U3.4, U4.11
GND: C3.2, C4.2, C5.2, C6.2, C7.2, C8.2, C9.2, C10.2, J2.1, J2.3, J2.5, J2.7, U1.1 (A), U1.8 (GND), U1.9 (A), U2.6 (GND), U3.7 (GND), U4.7 (GND), U5.7 (GND), U6.7 (GND), U7.7 (GND), U8.1 (GND), U9.1 (GND), μC1.19 (GNDi), μC1.39 (GNDii)
I2C_SCL: U8.3 (SCL), μC1.14 (B6)
I2C_SDA: U8.4 (SDA), μC1.15 (B7)
NEW_WRDATA: U5.9 (Q), μC1.13 (B5)
unnamed: R3.1, SW_BTN_ENTR1.1
unnamed: R4.1, SW_BTN_UP1.1
unnamed: R5.1, SW_BTN_DOWN1.1
unnamed: R6.1, SW_BTN_RET1.1
unnamed: C1.2, U1.14 (Cext)
unnamed: U1.3 (Clr), U4.2
unnamed: U1.13 (Q), U3.2
unnamed: C1.1, R1.1, U1.15 (RCext)
unnamed: C2.1, U1.6 (Cext)
unnamed: U1.5 (Q), U6.2 (MR), U6.12 (MR)
unnamed: C2.2, R2.1, U1.7 (RCext)
unnamed: U5.5 (Q), U7.2
unnamed: U5.12 (D), U7.3
unnamed: U6.6 (Q3), U6.13 (CP)
RDDATA: J2.16, R9.1, U3.3
SD_EJECT: U2.9 (CD), μC1.33 (A7)
SP1_MISO: U1.2 (B), μC1.32 (A6)
SP1_SCK: μC1.31 (A5)
SPI1_SCK: U4.1, μC1.12 (B4)
SPI2_MISO: U2.7 (DO), μC1.3 (B14)
SPI2_MOSI: U2.3 (DI), μC1.4 (B15)
SPI2_NSS: U2.2 (~CS), μC1.1 (B12)
SPI2_SCK: U2.5 (SCLK), μC1.2 (B13)
SPI3_SCK: U4.8, μC1.11 (B3)
STEP0: J2.2, μC1.26 (A0)
STEP1: J2.4, μC1.27 (A1)
STEP2: J2.6, μC1.28 (A2)
STEP3: J2.8, μC1.29 (A3)
TIM4: U6.1 (CP), μC1.16 (B8)
USART1_RX: μC1.7 (A10)
USART1_TX: μC1.6 (A9)
VCC: C3.1, C5.1, C6.1, C7.1, C8.1, C9.1, C10.1, J2.12, R1.2, R2.2, R3.2, R4.2, R5.2, R6.2, R7.2, R8.1, R9.2, U1.16 (VCC), U3.14 (VCC), U4.14 (VCC), U5.1 (~R), U5.4 (~S), U5.10 (~S), U5.14 (VCC), U6.14 (VCC), U7.14 (VCC), U9.3 (VI)
WRDATA: J2.18, U4.5
WRPROT: U3.5, μC1.35 (B1)
WR_PROTECT: J2.20, R8.2, U3.6
WR_REQ: J2.10, R7.1, U4.3, μC1.17 (B9)
/DRIVE_ENABLE: U4.10, μC1.30 (A4)

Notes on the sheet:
READ BLOC
LS393 counting to 16
WRITE BLOC
POWER BLOCK
TIM3 250KHz (255/128)
TIM4 32MHz (3/2)
